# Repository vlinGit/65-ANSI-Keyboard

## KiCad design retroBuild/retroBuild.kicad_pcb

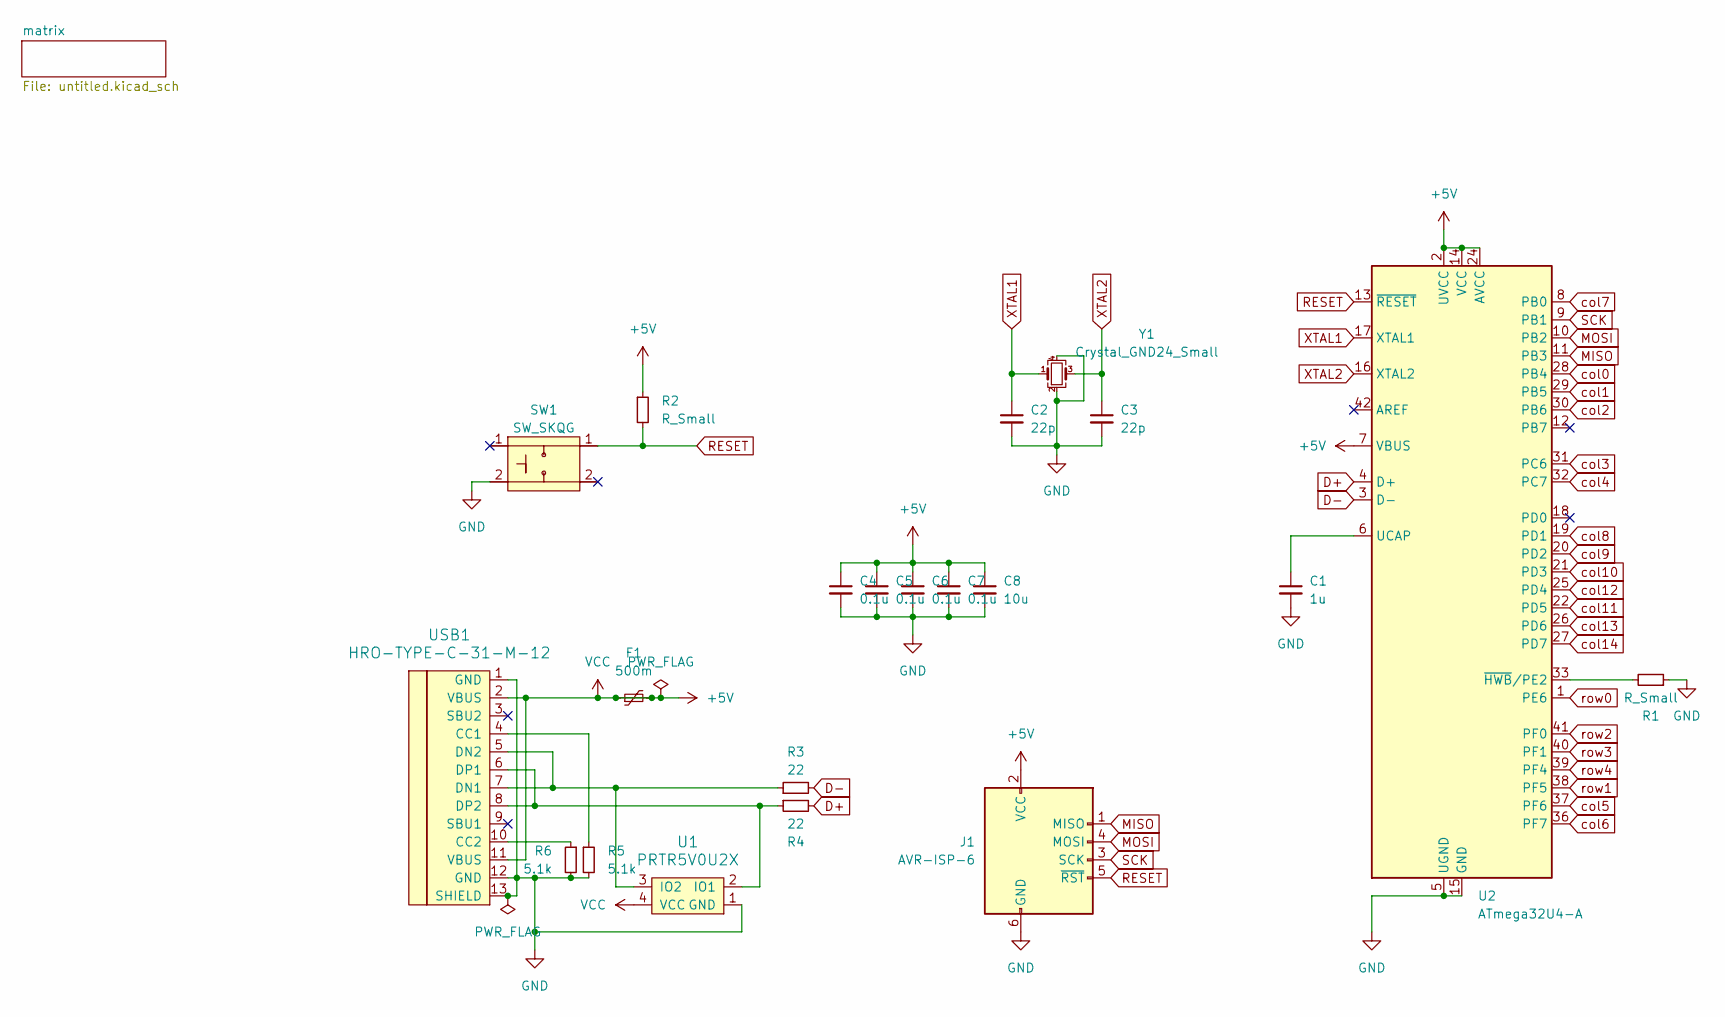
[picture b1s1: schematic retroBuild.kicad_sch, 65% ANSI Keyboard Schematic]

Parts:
C1: 1u; C_0805_2012Metric_Pad1.18x1.45mm_HandSolder
C2, C3: 22p; C_0805_2012Metric_Pad1.18x1.45mm_HandSolder
C4, C5, C6, C7: 0.1u; C_0805_2012Metric_Pad1.18x1.45mm_HandSolder
C8: 10u; C_0805_2012Metric_Pad1.18x1.45mm_HandSolder
F1: 500m; Fuse_1206_3216Metric_Pad1.42x1.75mm_HandSolder
J1: AVR-ISP-6; Reset_Pretty-Mask
R1, R2: R_Small; R_0805_2012Metric_Pad1.20x1.40mm_HandSolder
R3, R4: 22; R_0805_2012Metric_Pad1.20x1.40mm_HandSolder
R5, R6: 5.1k; R_0805_2012Metric_Pad1.20x1.40mm_HandSolder
SW1: SW_SKQG; SW_SPST_SKQG_WithStem
U1: PRTR5V0U2X; SOT143B
U2: ATmega32U4-A; TQFP-44_10x10mm_P0.8mm
USB1: HRO-TYPE-C-31-M-12; HRO-TYPE-C-31-M-12-HandSoldering
Y1: Crystal_GND24_Small; Crystal_SMD_3225-4Pin_3.2x2.5mm_HandSoldering

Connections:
+5V: C4.1, C5.1, C6.1, C7.1, C8.1, F1.1, F1.2, J1.2 (VCC), R2.1, U1.4 (VCC), U2.2 (UVCC), U2.7 (VBUS), U2.14 (VCC), U2.24 (AVCC), U2.34 (VCC), U2.44 (AVCC), USB1.2 (VBUS), USB1.11 (VBUS)
D+: R4.2, U2.4 (D+)
D-: R3.2, U2.3 (D-)
GND: C1.2, C2.2, C3.2, C4.2, C5.2, C6.2, C7.2, C8.2, J1.6 (GND), R1.1, R5.2, R6.2, SW1.2, U1.1 (GND), U2.5 (UGND), U2.15 (GND), U2.23 (GND), U2.35 (GND), U2.43 (GND), USB1.1 (GND), USB1.12 (GND), USB1.13 (SHIELD), Y1.2, Y1.4
MISO: J1.1 (MISO), U2.11 (PB3)
MOSI: J1.4 (MOSI), U2.10 (PB2)
unnamed: R4.1, U1.2 (IO1), USB1.6 (DP1), USB1.8 (DP2)
unnamed: R3.1, U1.3 (IO2), USB1.5 (DN2), USB1.7 (DN1)
unnamed: C1.1, U2.6 (UCAP)
unnamed: R1.2, U2.33 (~HWB/PE2)
unnamed: R5.1, USB1.4 (CC1)
unnamed: R6.1, USB1.10 (CC2)
RESET: J1.5 (~RST), R2.2, SW1.1, U2.13 (~RESET)
SCK: J1.3 (SCK), U2.9 (PB1)
XTAL1: C2.1, U2.17 (XTAL1), Y1.1
XTAL2: C3.1, U2.16 (XTAL2), Y1.3
col0: U2.28 (PB4); also elsewhere on the board
col1: U2.29 (PB5); also elsewhere on the board
col2: U2.30 (PB6); also elsewhere on the board
col3: U2.31 (PC6); also elsewhere on the board
col4: U2.32 (PC7); also elsewhere on the board
col5: U2.37 (PF6); also elsewhere on the board
col6: U2.36 (PF7); also elsewhere on the board
col7: U2.8 (PB0); also elsewhere on the board
col8: U2.19 (PD1); also elsewhere on the board
col9: U2.20 (PD2); also elsewhere on the board
col10: U2.21 (PD3); also elsewhere on the board
col11: U2.22 (PD5); also elsewhere on the board
col12: U2.25 (PD4); also elsewhere on the board
col13: U2.26 (PD6); also elsewhere on the board
col14: U2.27 (PD7); also elsewhere on the board
row0: U2.1 (PE6); also elsewhere on the board
row1: U2.38 (PF5); also elsewhere on the board
row2: U2.41 (PF0); also elsewhere on the board
row3: U2.40 (PF1); also elsewhere on the board
row4: U2.39 (PF4); also elsewhere on the board

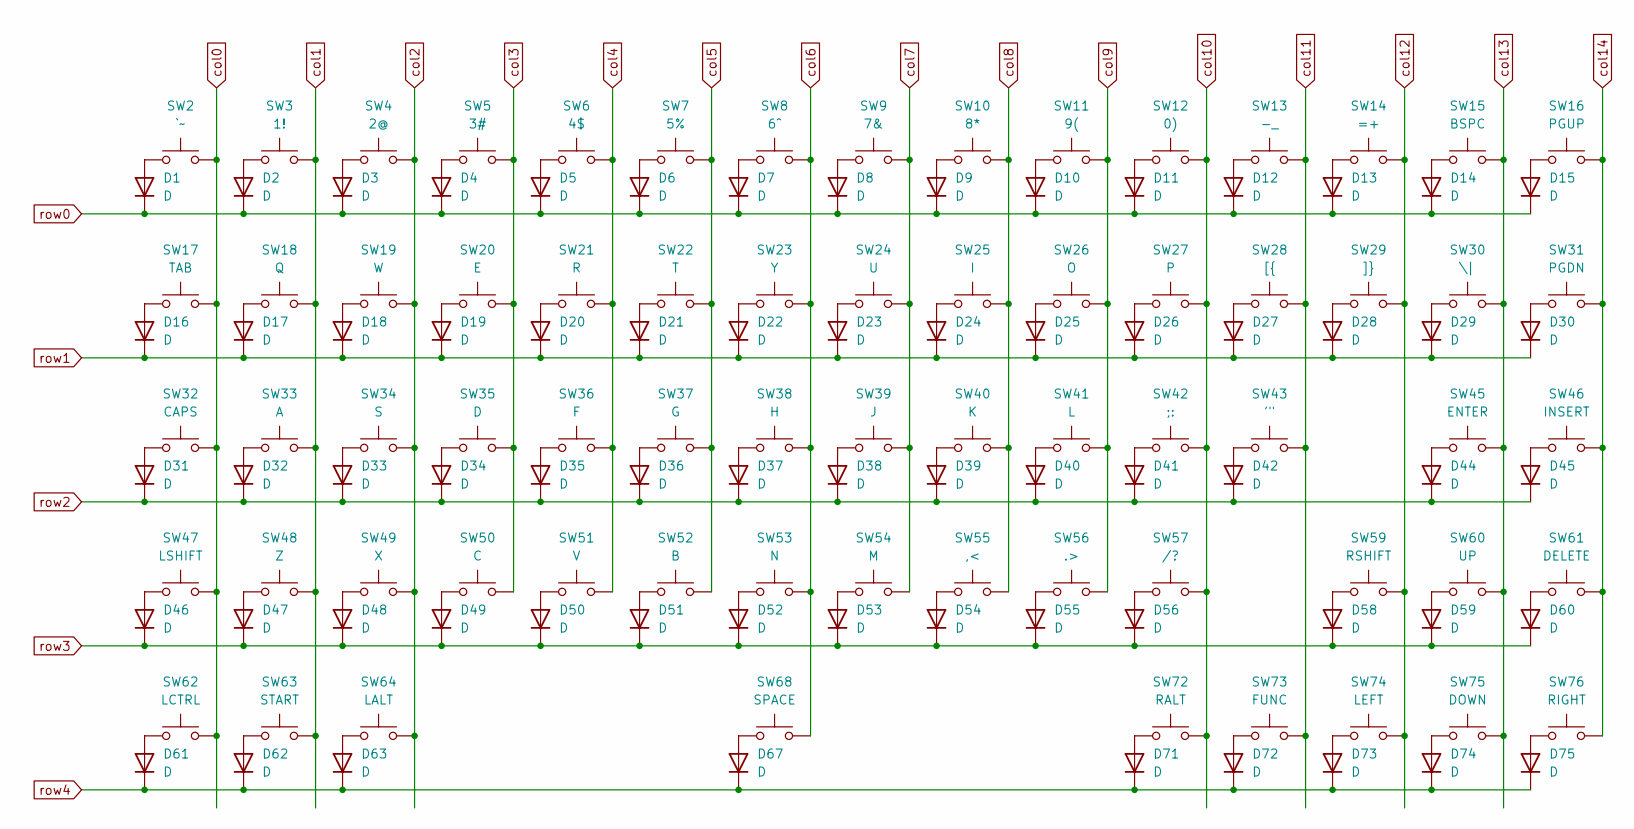
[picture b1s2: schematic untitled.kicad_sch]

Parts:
D1, D2, D3, D4, D5, D6, D7, D8, D9, D10, D11, D12, D13, D14, D15, D16, D17, D18, D19, D20, D21, D22, D23, D24, D25, D26, D27, D28, D29, D30, D31, D32, D33, D34, D35, D36, D37, D38, D39, D40, D41, D42, D44, D45, D46, D47, D48, D49, D50, D51, D52, D53, D54, D55, D56, D58, D59, D60, D61, D62, D63, D67, D71, D72, D73, D74, D75: D; D_SOD-123
SW2: `~; MX-Alps-Hybrid-1U
SW3: 1!; MX-Alps-Hybrid-1U
SW4: 2@; MX-Alps-Hybrid-1U
SW5: 3#; MX-Alps-Hybrid-1U
SW6: 4$; MX-Alps-Hybrid-1U
SW7: 5%; MX-Alps-Hybrid-1U
SW8: 6^; MX-Alps-Hybrid-1U
SW9: 7&; MX-Alps-Hybrid-1U
SW10: 8*; MX-Alps-Hybrid-1U
SW11: 9(; MX-Alps-Hybrid-1U
SW12: 0); MX-Alps-Hybrid-1U
SW13: -_; MX-Alps-Hybrid-1U
SW14: =+; MX-Alps-Hybrid-1U
SW15: BSPC; MX-Alps-Hybrid-2U
SW16: PGUP; MX-Alps-Hybrid-1U
SW17: TAB; MX-Alps-Hybrid-1.5U
SW18: Q; MX-Alps-Hybrid-1U
SW19: W; MX-Alps-Hybrid-1U
SW20: E; MX-Alps-Hybrid-1U
SW21: R; MX-Alps-Hybrid-1U
SW22: T; MX-Alps-Hybrid-1U
SW23: Y; MX-Alps-Hybrid-1U
SW24: U; MX-Alps-Hybrid-1U
SW25: I; MX-Alps-Hybrid-1U
SW26: O; MX-Alps-Hybrid-1U
SW27: P; MX-Alps-Hybrid-1U
SW28: [{; MX-Alps-Hybrid-1U
SW29: ]}; MX-Alps-Hybrid-1U
SW30: \|; MX-Alps-Hybrid-1.5U
SW31: PGDN; MX-Alps-Hybrid-1U
SW32: CAPS; MX-Alps-Hybrid-1.75U
SW33: A; MX-Alps-Hybrid-1U
SW34: S; MX-Alps-Hybrid-1U
SW35: D; MX-Alps-Hybrid-1U
SW36: F; MX-Alps-Hybrid-1U
SW37: G; MX-Alps-Hybrid-1U
SW38: H; MX-Alps-Hybrid-1U
SW39: J; MX-Alps-Hybrid-1U
SW40: K; MX-Alps-Hybrid-1U
SW41: L; MX-Alps-Hybrid-1U
SW42: ;:; MX-Alps-Hybrid-1U
SW43: '"; MX-Alps-Hybrid-1U
SW45: ENTER; MX-Alps-Hybrid-2.25U
SW46: INSERT; MX-Alps-Hybrid-1U
SW47: LSHIFT; MX-Alps-Hybrid-2.25U
SW48: Z; MX-Alps-Hybrid-1U
SW49: X; MX-Alps-Hybrid-1U
SW50: C; MX-Alps-Hybrid-1U
SW51: V; MX-Alps-Hybrid-1U
SW52: B; MX-Alps-Hybrid-1U
SW53: N; MX-Alps-Hybrid-1U
SW54: M; MX-Alps-Hybrid-1U
SW55: ,<; MX-Alps-Hybrid-1U
SW56: .>; MX-Alps-Hybrid-1U
SW57: /?; MX-Alps-Hybrid-1U
SW59: RSHIFT; MX-Alps-Hybrid-1.75U
SW60: UP; MX-Alps-Hybrid-1U
SW61: DELETE; MX-Alps-Hybrid-1U
SW62: LCTRL; MX-Alps-Hybrid-1.25U
SW63: START; MX-Alps-Hybrid-1.25U
SW64: LALT; MX-Alps-Hybrid-1.25U
SW68: SPACE; MX-Alps-Hybrid-6.25U
SW72: RALT; MX-Alps-Hybrid-1.25U
SW73: FUNC; MX-Alps-Hybrid-1.25U
SW74: LEFT; MX-Alps-Hybrid-1U
SW75: DOWN; MX-Alps-Hybrid-1U
SW76: RIGHT; MX-Alps-Hybrid-1U

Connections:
unnamed: D1.2 (A), SW2.1
unnamed: D2.2 (A), SW3.1
unnamed: D3.2 (A), SW4.1
unnamed: D4.2 (A), SW5.1
unnamed: D5.2 (A), SW6.1
unnamed: D6.2 (A), SW7.1
unnamed: D7.2 (A), SW8.1
unnamed: D8.2 (A), SW9.1
unnamed: D9.2 (A), SW10.1
unnamed: D10.2 (A), SW11.1
unnamed: D11.2 (A), SW12.1
unnamed: D12.2 (A), SW13.1
unnamed: D13.2 (A), SW14.1
unnamed: D14.2 (A), SW15.1
unnamed: D15.2 (A), SW16.1
unnamed: D16.2 (A), SW17.1
unnamed: D17.2 (A), SW18.1
unnamed: D18.2 (A), SW19.1
unnamed: D19.2 (A), SW20.1
unnamed: D20.2 (A), SW21.1
unnamed: D21.2 (A), SW22.1
unnamed: D22.2 (A), SW23.1
unnamed: D23.2 (A), SW24.1
unnamed: D24.2 (A), SW25.1
unnamed: D25.2 (A), SW26.1
unnamed: D26.2 (A), SW27.1
unnamed: D27.2 (A), SW28.1
unnamed: D28.2 (A), SW29.1
unnamed: D29.2 (A), SW30.1
unnamed: D30.2 (A), SW31.1
unnamed: D31.2 (A), SW32.1
unnamed: D32.2 (A), SW33.1
unnamed: D33.2 (A), SW34.1
unnamed: D34.2 (A), SW35.1
unnamed: D35.2 (A), SW36.1
unnamed: D36.2 (A), SW37.1
unnamed: D37.2 (A), SW38.1
unnamed: D38.2 (A), SW39.1
unnamed: D39.2 (A), SW40.1
unnamed: D40.2 (A), SW41.1
unnamed: D41.2 (A), SW42.1
unnamed: D42.2 (A), SW43.1
unnamed: D44.2 (A), SW45.1
unnamed: D45.2 (A), SW46.1
unnamed: D46.2 (A), SW47.1
unnamed: D47.2 (A), SW48.1
unnamed: D48.2 (A), SW49.1
unnamed: D49.2 (A), SW50.1
unnamed: D50.2 (A), SW51.1
unnamed: D51.2 (A), SW52.1
unnamed: D52.2 (A), SW53.1
unnamed: D53.2 (A), SW54.1
unnamed: D54.2 (A), SW55.1
unnamed: D55.2 (A), SW56.1
unnamed: D56.2 (A), SW57.1
unnamed: D58.2 (A), SW59.1
unnamed: D59.2 (A), SW60.1
unnamed: D60.2 (A), SW61.1
unnamed: D61.2 (A), SW62.1
unnamed: D62.2 (A), SW63.1
unnamed: D63.2 (A), SW64.1
unnamed: D67.2 (A), SW68.1
unnamed: D71.2 (A), SW72.1
unnamed: D72.2 (A), SW73.1
unnamed: D73.2 (A), SW74.1
unnamed: D74.2 (A), SW75.1
unnamed: D75.2 (A), SW76.1
col0: SW2.2, SW17.2, SW32.2, SW47.2, SW62.2; also elsewhere on the board
col1: SW3.2, SW18.2, SW33.2, SW48.2, SW63.2; also elsewhere on the board
col2: SW4.2, SW19.2, SW34.2, SW49.2, SW64.2; also elsewhere on the board
col3: SW5.2, SW20.2, SW35.2, SW50.2; also elsewhere on the board
col4: SW6.2, SW21.2, SW36.2, SW51.2; also elsewhere on the board
col5: SW7.2, SW22.2, SW37.2, SW52.2; also elsewhere on the board
col6: SW8.2, SW23.2, SW38.2, SW53.2, SW68.2; also elsewhere on the board
col7: SW9.2, SW24.2, SW39.2, SW54.2; also elsewhere on the board
col8: SW10.2, SW25.2, SW40.2, SW55.2; also elsewhere on the board
col9: SW11.2, SW26.2, SW41.2, SW56.2; also elsewhere on the board
col10: SW12.2, SW27.2, SW42.2, SW57.2, SW72.2; also elsewhere on the board
col11: SW13.2, SW28.2, SW43.2, SW73.2; also elsewhere on the board
col12: SW14.2, SW29.2, SW59.2, SW74.2; also elsewhere on the board
col13: SW15.2, SW30.2, SW45.2, SW60.2, SW75.2; also elsewhere on the board
col14: SW16.2, SW31.2, SW46.2, SW61.2, SW76.2; also elsewhere on the board
row0: D1.1 (K), D2.1 (K), D3.1 (K), D4.1 (K), D5.1 (K), D6.1 (K), D7.1 (K), D8.1 (K), D9.1 (K), D10.1 (K), D11.1 (K), D12.1 (K), D13.1 (K), D14.1 (K), D15.1 (K); also elsewhere on the board
row1: D16.1 (K), D17.1 (K), D18.1 (K), D19.1 (K), D20.1 (K), D21.1 (K), D22.1 (K), D23.1 (K), D24.1 (K), D25.1 (K), D26.1 (K), D27.1 (K), D28.1 (K), D29.1 (K), D30.1 (K); also elsewhere on the board
row2: D31.1 (K), D32.1 (K), D33.1 (K), D34.1 (K), D35.1 (K), D36.1 (K), D37.1 (K), D38.1 (K), D39.1 (K), D40.1 (K), D41.1 (K), D42.1 (K), D44.1 (K), D45.1 (K); also elsewhere on the board
row3: D46.1 (K), D47.1 (K), D48.1 (K), D49.1 (K), D50.1 (K), D51.1 (K), D52.1 (K), D53.1 (K), D54.1 (K), D55.1 (K), D56.1 (K), D58.1 (K), D59.1 (K), D60.1 (K); also elsewhere on the board
row4: D61.1 (K), D62.1 (K), D63.1 (K), D67.1 (K), D71.1 (K), D72.1 (K), D73.1 (K), D74.1 (K), D75.1 (K); also elsewhere on the board

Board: 2 copper layers, 155 parts (1 on the bottom side), 103 nets, no tracks yet.

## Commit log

2024-03-21 keys layed out in pcb view
